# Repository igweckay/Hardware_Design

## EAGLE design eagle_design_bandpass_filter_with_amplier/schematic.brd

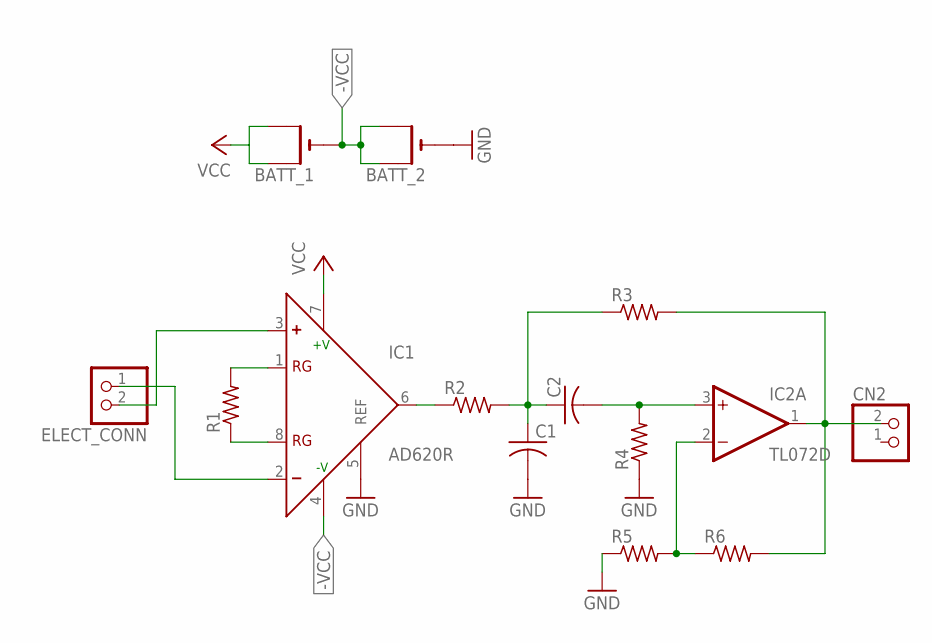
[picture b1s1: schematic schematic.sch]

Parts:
BATT_1, BATT_2: CR1220SMT; CR1220-SMD
C1, C2: C-USC0805; C0805
CN2: JST_2PIN-SMT-RA; JST-PH-2-SMT-RA
ELECT_CONN: JST_2PIN-SMT-RA; JST-PH-2-SMT-RA
IC1: AD620R; SO8
IC2: TL072D; SO08
R1, R2, R3, R4, R5, R6: R-US_R0805; R0805

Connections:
-VCC: BATT_1.-, BATT_2.+$1 (+), BATT_2.+$2 (+1), IC1.4 (-V)
GND: BATT_2.-, C1.2, IC1.5 (REF), R4.1, R5.1
unnamed: IC1.1 (RG), R1.2
unnamed: IC1.8 (RG), R1.1
unnamed: IC1.6 (OUT), R2.1
unnamed: C1.1, C2.1, R2.2, R3.1
unnamed: C2.2, IC2.3 (+IN), R4.2
unnamed: CN2.2 (1), IC2.1 (OUT), R3.2, R6.2
unnamed: IC2.2 (-IN), R5.2, R6.1
unnamed: ELECT_CONN.2 (1), IC1.3 (+)
unnamed: ELECT_CONN.1 (2), IC1.2 (-)
V+: IC2.8 (V+)
V-: IC2.4 (V-)
VCC: BATT_1.+$1 (+), BATT_1.+$2 (+1), IC1.7 (+V)

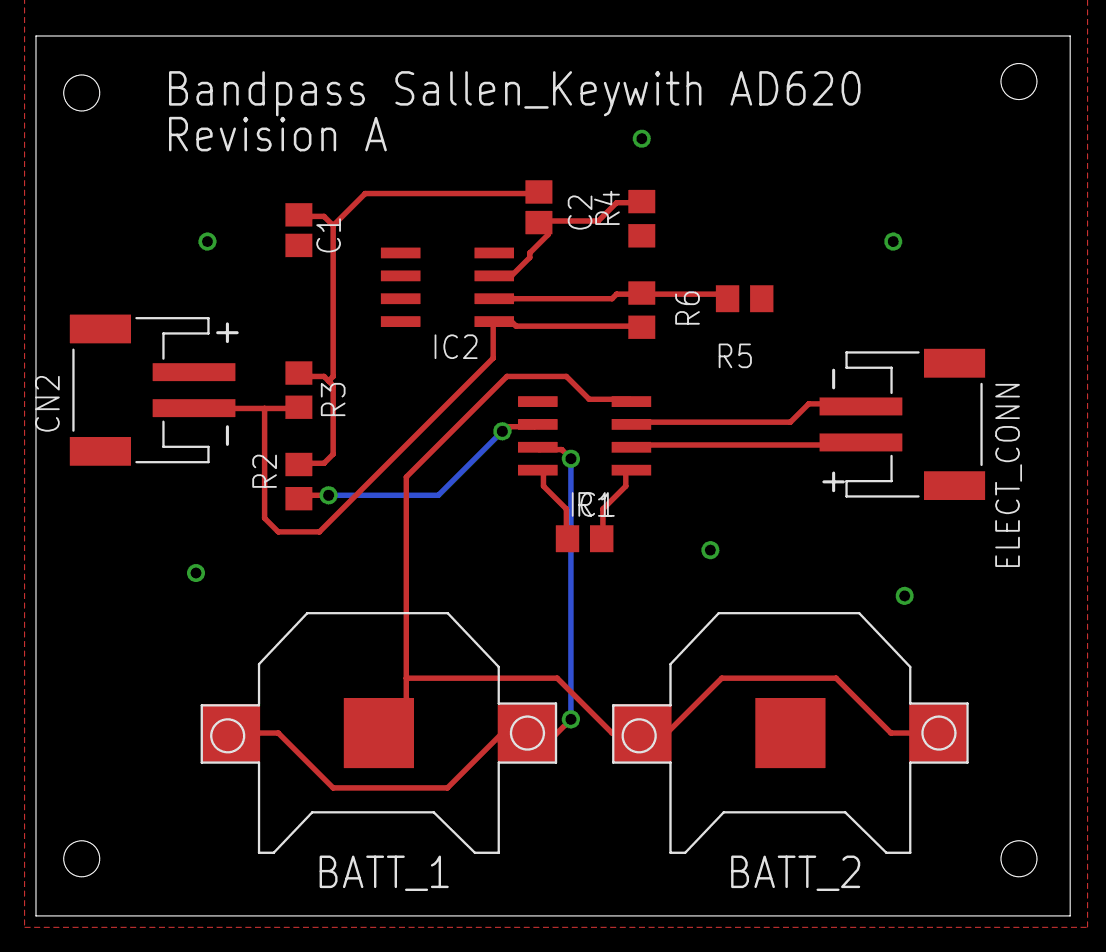
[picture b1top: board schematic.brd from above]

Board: 2 copper layers, 57.5 x 48.9 mm, 14 parts (0 on the bottom side), 12 nets.

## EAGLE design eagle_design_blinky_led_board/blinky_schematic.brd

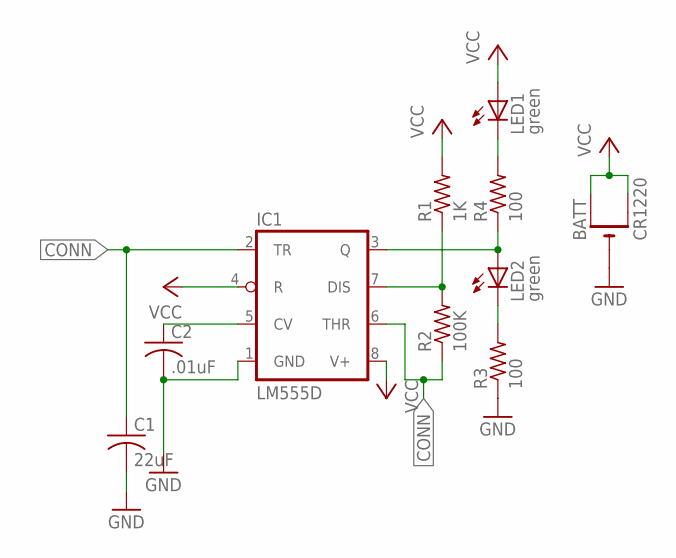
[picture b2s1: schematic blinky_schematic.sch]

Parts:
BATT: CR1220; CR1220-SMD; MPN 3080
C1: 22uF; C0805; MPN F981A226MSAAS1
C2: .01uF; C0805; MPN 0805PC103KAZ1A
IC1: LM555D; SO08; MPN 1526
LED1, LED2: green; CHIPLED_0805; MPN 5988170107F
R1: 1K; R0805; MPN ERJ-6ENF1601V
R2: 100K; R0805; MPN CRCW0805100KFKTA
R3, R4: 100; R0805; MPN MCHP05W4F1000T5E

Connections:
CONN: C1.1, IC1.2 (TR), IC1.6 (THR), R2.1
GND: BATT.-, C1.2, C2.2, IC1.1 (GND), R3.1
unnamed: LED1.C, R4.2
unnamed: IC1.3 (Q), LED2.A, R4.1
unnamed: LED2.C, R3.2
unnamed: IC1.7 (DIS), R1.1, R2.2
unnamed: C2.1, IC1.5 (CV)
VCC: BATT.+$1 (+), BATT.+$2 (+1), IC1.4 (R), IC1.8 (V+), LED1.A, R1.2

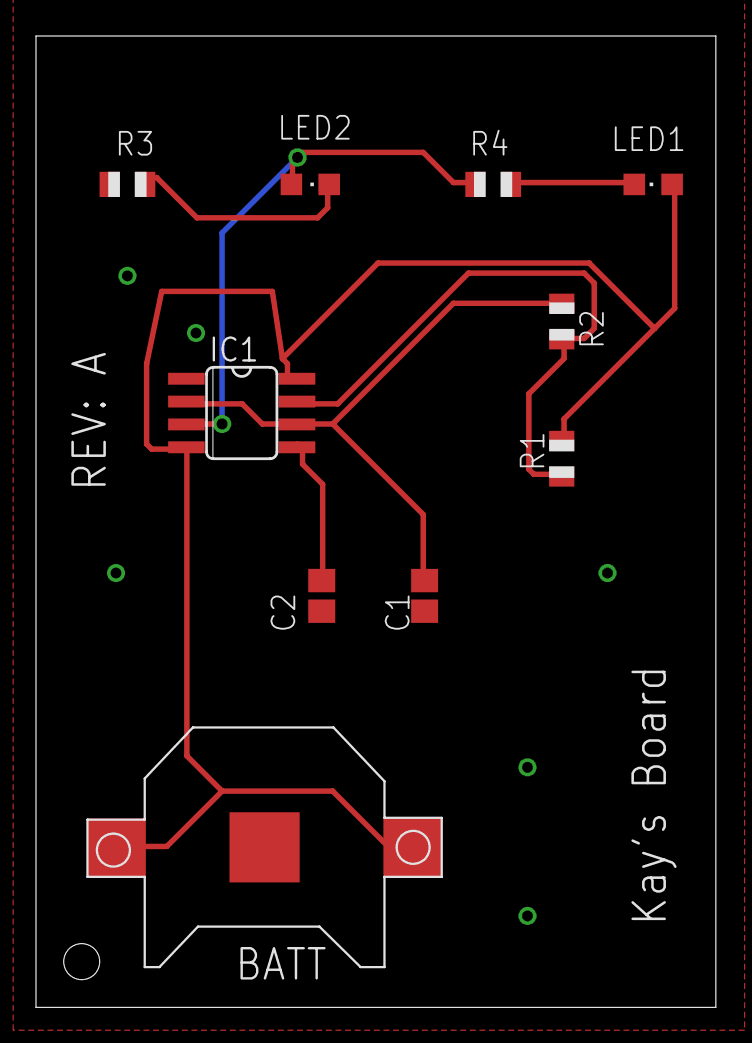
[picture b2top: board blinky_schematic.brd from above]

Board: 2 copper layers, 37.8 x 54.0 mm, 10 parts (0 on the bottom side), 8 nets.

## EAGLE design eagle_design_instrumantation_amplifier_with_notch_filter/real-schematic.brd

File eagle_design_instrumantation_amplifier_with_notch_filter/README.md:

# Eagle-Design-Intrument.-with-LowPass-ith-Twin-Notch-FIlter
Instrumentation amplifier with 2 stage 3rd order sallen- key low pass filter with twin notch filter at 60Hz

The design will really use the TLC272 ic. The schematic-real.sch was used in order to route all of the connections where they should go. The TLC271 was used here because it is the same size and has the same packaging as the TLC272. The TLC272 design was not used for routing becuase it lacked connection pins to GND and VCC. For some reason, the schematic for the TLC272 does not have connection pins to VCC and GND, and so those connections are not able to be connected. The TLC271 was used to correct for this design flaw.

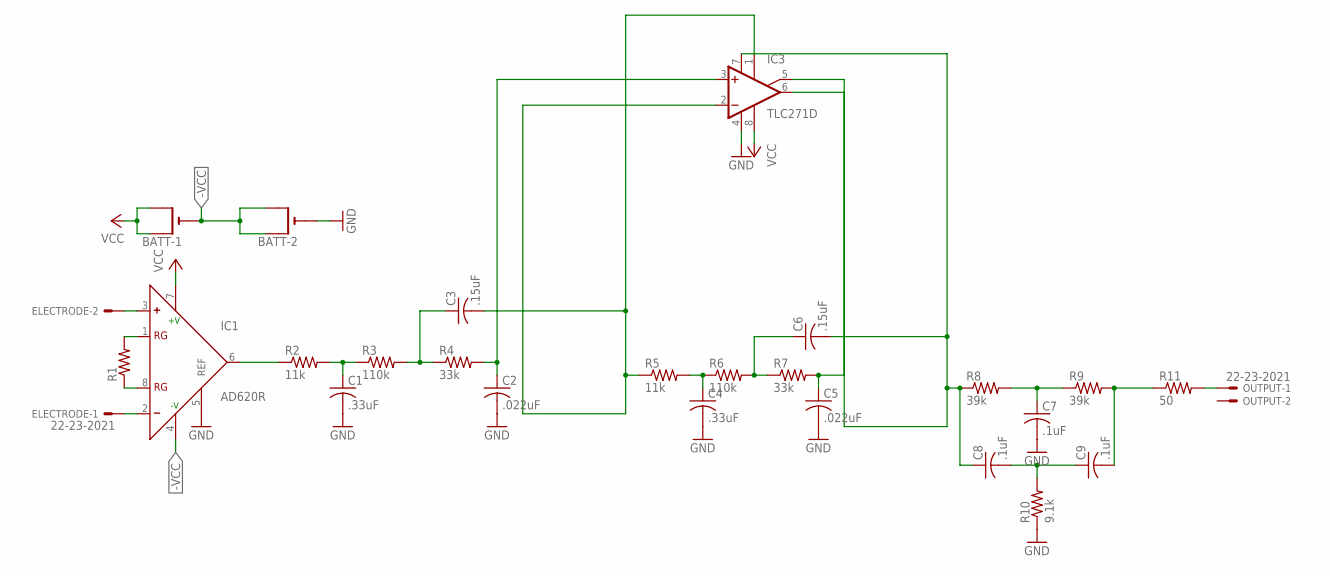
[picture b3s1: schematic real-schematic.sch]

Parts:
BATT-1, BATT-2: CR1220SMT; CR1220-SMD
C1, C4: .33uF; C0805
C2, C5: .022uF; C0805
C3, C6: .15uF; C0805
C7, C8, C9: .1uF; C0805
ELECTRODE: 22-23-2021
IC1: AD620R; SO8
IC3: TLC271D; SO08
OUTPUT: 22-23-2021
R1: R-US_R0805; R0805
R2, R5: 11k; R0805
R3, R6: 110k; R0805
R4, R7: 33k; R0805
R8, R9: 39k; R0805
R10: 9.1k; R0805
R11: 50; R0805

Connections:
-VCC: BATT-1.-, BATT-2.+$1 (+), BATT-2.+$2 (+1), IC1.4 (-V)
GND: BATT-2.-, C1.2, C2.2, C4.2, C5.2, C7.2, IC1.5 (REF), IC3.4 (V-), R10.1
unnamed: C4.1, R5.2, R6.1
unnamed: IC1.6 (OUT), R2.1
unnamed: C1.1, R2.2, R3.1
unnamed: C3.1, R3.2, R4.1
unnamed: C2.1, IC3.3 (+IN), R4.2
unnamed: C3.2, IC3.1 (ON1), IC3.2 (-IN), R5.1
unnamed: C6.1, R6.2, R7.1
unnamed: C5.1, IC3.5 (ON2), R7.2
unnamed: C6.2, C8.1, IC3.6 (OUT), IC3.7 (V+), R8.1
unnamed: C7.1, R8.2, R9.1
unnamed: C9.2, R9.2, R11.1
unnamed: C8.2, C9.1, R10.2
unnamed: IC1.1 (RG), R1.2
unnamed: IC1.8 (RG), R1.1
unnamed: ELECTRODE.2, IC1.3 (+)
unnamed: ELECTRODE.1, IC1.2 (-)
unnamed: OUTPUT.1, R11.2
VCC: BATT-1.+$1 (+), BATT-1.+$2 (+1), IC1.7 (+V), IC3.8 (OPT)

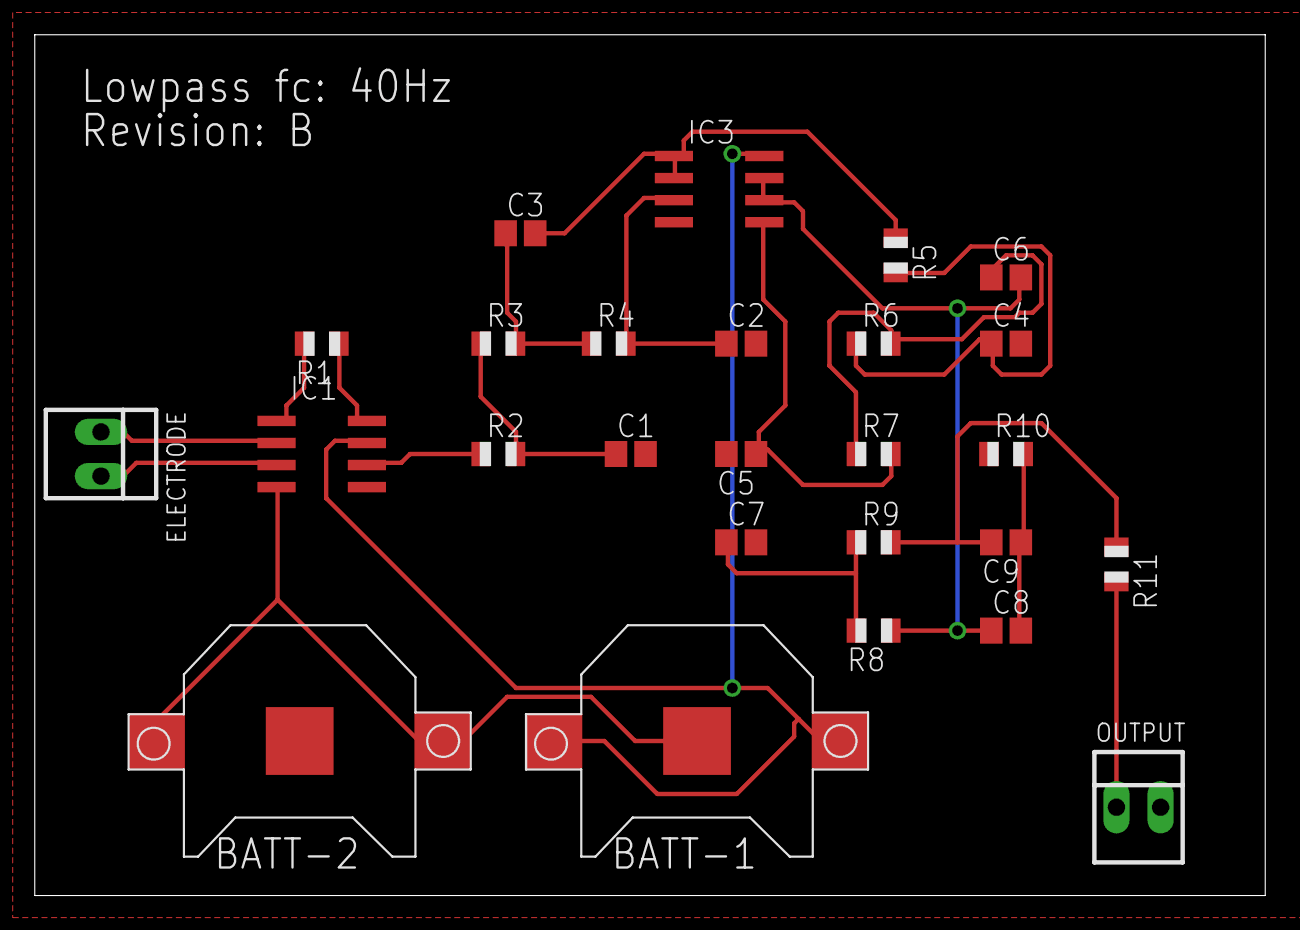
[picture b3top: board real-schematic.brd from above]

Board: 2 copper layers, 70.8 x 49.5 mm, 26 parts (0 on the bottom side), 20 nets.

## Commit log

2017-04-11 added 4 design repos
2018-06-28 added Benchtop Cardiac Pacemaker folder to Hardware_Designs
